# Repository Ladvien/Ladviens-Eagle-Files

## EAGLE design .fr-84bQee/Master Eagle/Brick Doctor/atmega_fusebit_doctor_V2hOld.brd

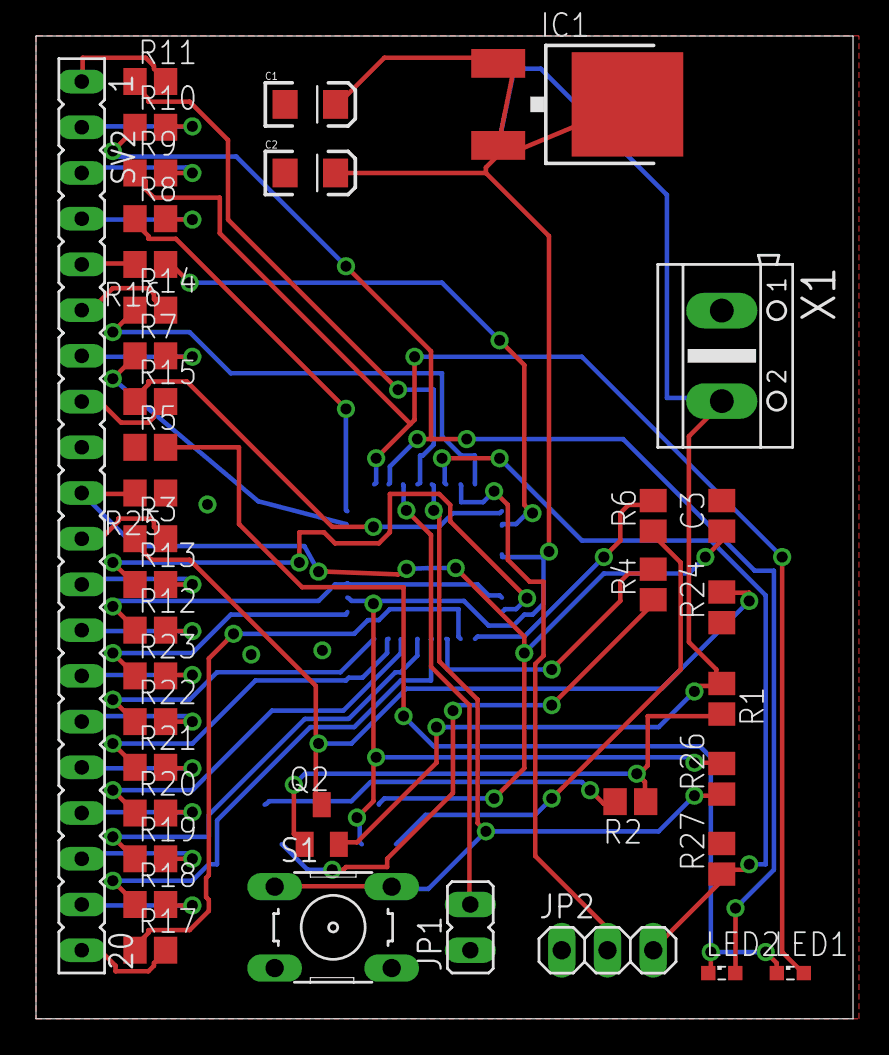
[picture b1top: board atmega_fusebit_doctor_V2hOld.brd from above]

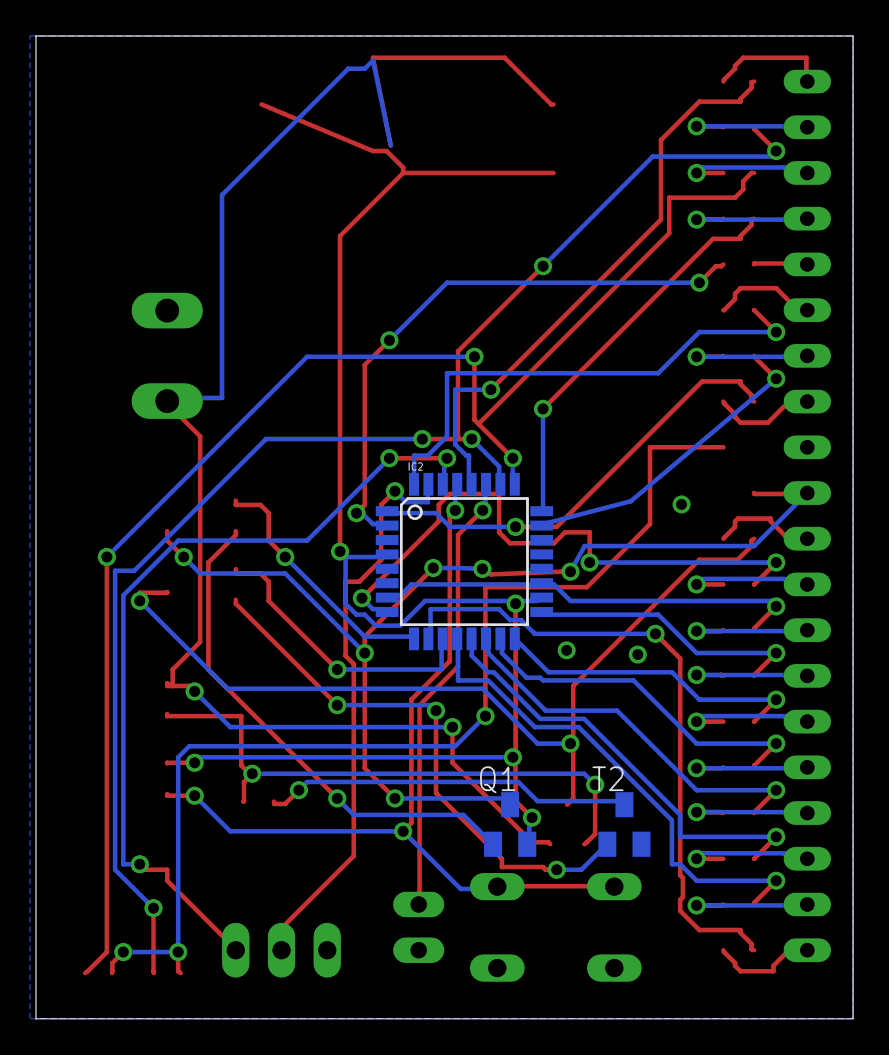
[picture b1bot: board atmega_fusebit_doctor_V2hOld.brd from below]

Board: 2 copper layers, 45.4 x 54.6 mm, 42 parts (3 on the bottom side), 51 nets.

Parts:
C1: 100uF; EIA3216
C2: 10uF; EIA3216
C3: 10nF; C0805
IC1: 7805; V-REG_DPACK
IC2: ATMEGA8-DOC; TQFP32-08
JP1: ERASE; JP1
JP2: RS232; 1X03
LED1: red; SML0603
LED2: green; SML0603
Q1, Q2: BC857ALT1SMD; SOT23-BEC
R1, R27: 10K; R0805
R2, R7, R8, R9, R10, R11, R12, R13, R14, R15, R16, R17, R18, R19, R20, R21, R22, R23, R24, R26: 1K; R0805
R3, R25: 100; R0805
R4, R6: 4K7; R0805
R5: 330; R0805
S1: START; B3F-10XX
SV2: FE20
T2: BC847; SOT23
X1: AK500/2

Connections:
+5V: C3.1, Q1.C, R25.2, SV2.10
+12V: R3.2, SV2.11
BS1: R8.2, SV2.4
BS2: R17.2, SV2.20
DATA0: R18.2, SV2.19
DATA1: R19.2, SV2.18
DATA2: R20.2, SV2.17
DATA3: R21.2, SV2.16
DATA4: R22.2, SV2.15
DATA5: R23.2, SV2.14
DATA6: R12.2, SV2.13
DATA7: R13.2, SV2.12
GND: C1.C, C2.C, C3.2, IC1.1, IC2.3, IC2.21, JP1.1, JP2.1, R5.1, R24.1, R25.1, R27.2, S1.3, S1.4, SV2.9, T2.2, X1.1
unnamed: Q1.B, R6.1
unnamed: IC2.12, R18.1
unnamed: IC2.31, JP2.2
unnamed: IC2.28, R11.1
unnamed: IC2.2, R16.1
unnamed: IC2.32, R14.1
unnamed: IC2.30, JP2.3, R27.1
unnamed: R2.2, T2.3
unnamed: IC2.7, IC2.19, R12.1
unnamed: IC2.8, R13.1
unnamed: IC2.11, R4.2
unnamed: IC2.9, R6.2
unnamed: IC2.13, R19.1
unnamed: IC2.14, R20.1
unnamed: IC2.1, R15.1
unnamed: IC2.23, R7.1
unnamed: Q2.C, R3.1, R24.2
unnamed: IC2.15, R21.1
unnamed: IC2.16, R22.1
unnamed: IC2.17, R23.1
unnamed: IC2.10, R17.1
unnamed: R4.1, T2.1
unnamed: IC2.27, JP1.2
unnamed: LED1.C, LED2.C, R5.2
unnamed: Q2.B, R1.2, R2.1
unnamed: IC2.24, R8.1
unnamed: IC2.29, R26.1, S1.1, S1.2
unnamed: IC2.26, LED2.A, R10.1
unnamed: IC2.25, LED1.A, R9.1
OE: R14.2, SV2.6
PAG: R11.2, SV2.1
RDY: R7.2, SV2.7
V+: C1.A, IC1.3, Q2.E, R1.1, X1.2
VCC: C2.A, IC1.4, IC2.4, IC2.18, Q1.E, R26.2
WR: R16.2, SV2.5
XA0: R9.2, SV2.3
XA1: R10.2, SV2.2
XTAL1: R15.2, SV2.8

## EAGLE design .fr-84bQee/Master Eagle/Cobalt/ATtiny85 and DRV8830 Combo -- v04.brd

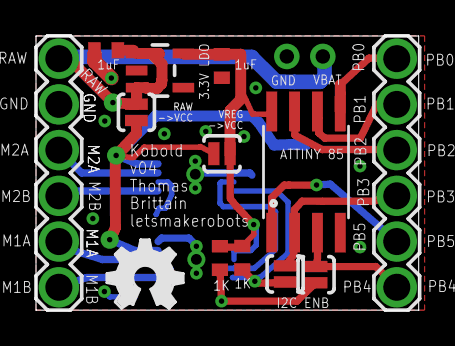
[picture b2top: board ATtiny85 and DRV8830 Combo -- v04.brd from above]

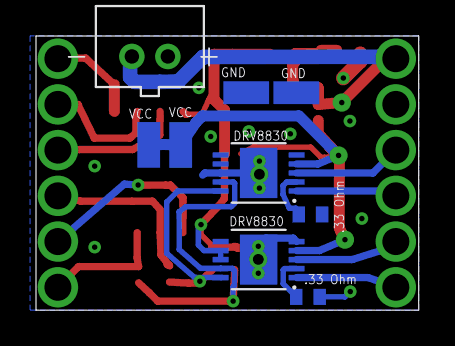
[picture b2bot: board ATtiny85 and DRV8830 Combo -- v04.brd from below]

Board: 2 copper layers, 21.3 x 15.2 mm, 22 parts (9 on the bottom side), 18 nets.

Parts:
1K: R3; R0402
C1, C2: 1uf; C0402
CN1: JST-PH-2-THM
PAD1, PAD2, PAD3, PAD4: SMD1,27-2,54
R1, R3: .33; R0402
R2: 1k; R0402
RAW: SOLDERJUMPERNO; SJ_2S-NO
SJ6, SJ7: SOLDERJUMPERNO; SJ_2S-NO
U1: V_REG_LDOSMD; SOT23-5
U2, U3: DRV8830; MSOP-10-GNDPAD
U$1, U$4: 1X6_SHORT_ROUND
U$2: ATTINY85; SO08-EIAJ
U$3: OSHW_FILLX150_NOTEXT
VREG: SOLDERJUMPERNO; SJ_2S-NO

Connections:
BAT_RAW: C1.1, CN1.2, RAW.1, U1.1, U1.3, U$4.1
GND: C1.2, C2.2, CN1.1, PAD1.1, PAD3.1, R1.1, R3.1, U1.2, U2.5, U2.GND, U3.5, U3.7, U3.8, U3.GND, U$2.4, U$4.2
M1_A: U2.3, U$4.5
M1_B: U2.1, U$4.6
M2_A: U3.3, U$4.3
M2_B: U3.1, U$4.4
unnamed: R1.2, U3.2
unnamed: R3.2, U2.2
PB0: U$1.1, U$2.5
PB1: U$1.2, U$2.6
PB2: U$1.3, U$2.7
PB3: SJ7.2, U$1.4, U$2.2
PB4: SJ6.2, U$1.6, U$2.3
PB5: U$1.5, U$2.1
SCL: R2.2, SJ7.1, U2.10, U3.10
SDA: 1K.2, SJ6.1, U2.9, U3.9
VCC: PAD2.1, PAD4.1, RAW.2, U2.4, U3.4, VREG.2
VREG: 1K.1, C2.1, R2.1, U1.5, U2.7, U2.8, U$2.8, VREG.1

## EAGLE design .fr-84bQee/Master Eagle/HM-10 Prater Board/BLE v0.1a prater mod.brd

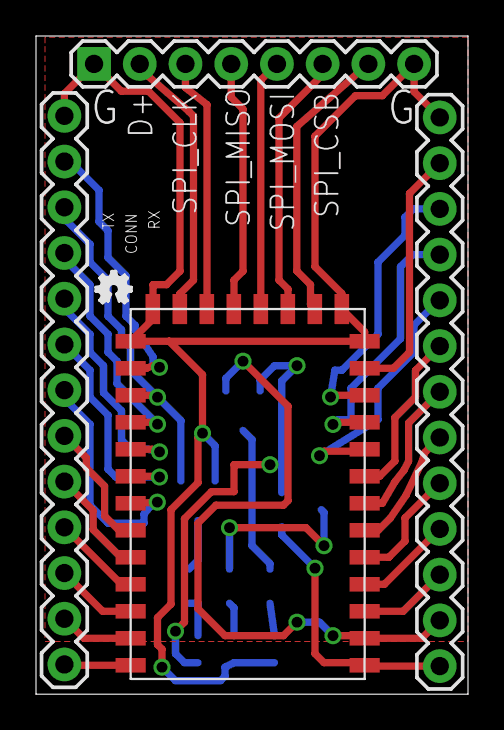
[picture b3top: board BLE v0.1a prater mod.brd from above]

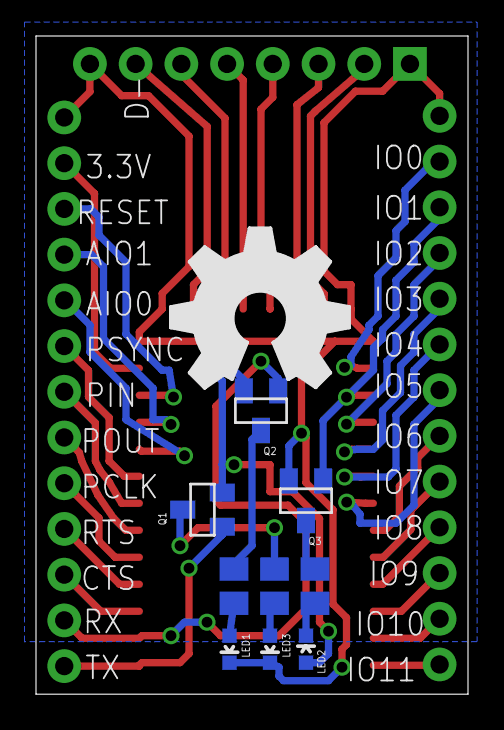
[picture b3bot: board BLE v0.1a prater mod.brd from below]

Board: 2 copper layers, 24.0 x 36.6 mm, 15 parts (10 on the bottom side), 38 nets.

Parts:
JP1, JP2: M13; 1X13
JP3: 1X08
LED1, LED2, LED3: LED-0603
Q1, Q2: MMBT3906; SOT23
Q3: MMBT2222A; SOT23
R7, R8, R9: 220; M0805
U$1: BLE-HM-10
U$2: OSHW_FILLX350_NOTEXT
U$3: OSHW_FILLX70_NOTEXT

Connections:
3.3V: LED2.A, Q1.2, Q2.2
GND: JP1.1, JP2.13, JP3.1, JP3.8, LED1.C, LED3.C, Q3.2, U$1.GND1, U$1.GND2, U$1.GND3, U$1.GND4
HVTX->LVRX: JP1.12, Q2.1, U$1.UART_RX
LVRX->HVTX: JP1.13, Q1.1, U$1.UART_TX
unnamed: Q3.3, R7.1
unnamed: JP1.3, U$1.RESET
unnamed: JP1.4, U$1.AIO1
unnamed: JP1.5, U$1.AIO0
unnamed: JP1.6, U$1.PCM_SYNC
unnamed: JP1.7, U$1.PCM_IN
unnamed: JP1.8, U$1.PCM_OUT
unnamed: JP1.9, U$1.PCM_CLK
unnamed: JP1.10, U$1.UART_RTS
unnamed: JP1.11, U$1.UART_CTS
unnamed: JP2.1, U$1.PIO11
unnamed: JP2.2, U$1.PIO10
unnamed: JP2.3, U$1.PIO9
unnamed: JP2.4, U$1.PIO8
unnamed: JP2.5, U$1.PIO7
unnamed: JP2.6, U$1.PIO6
unnamed: JP2.7, U$1.PIO5
unnamed: JP2.8, U$1.PIO4
unnamed: JP2.9, U$1.PIO3
unnamed: JP2.10, U$1.PIO2
unnamed: JP2.11, Q3.1, U$1.PIO1
unnamed: LED2.C, R7.2
unnamed: JP3.2, U$1.USB_D+
unnamed: JP3.3, U$1.SPI_CLK
unnamed: JP3.4, U$1.SPI_MISO
unnamed: JP3.5, U$1.SPI_MOSI
unnamed: JP3.6, U$1.SPI_CSB
unnamed: JP3.7, U$1.USB_D-
unnamed: Q2.3, R9.2
unnamed: LED1.A, R9.1
unnamed: LED3.A, R8.1
unnamed: Q1.3, R8.2
unnamed: JP1.2, U$1.3.3V
unnamed: JP2.12, U$1.PIO0

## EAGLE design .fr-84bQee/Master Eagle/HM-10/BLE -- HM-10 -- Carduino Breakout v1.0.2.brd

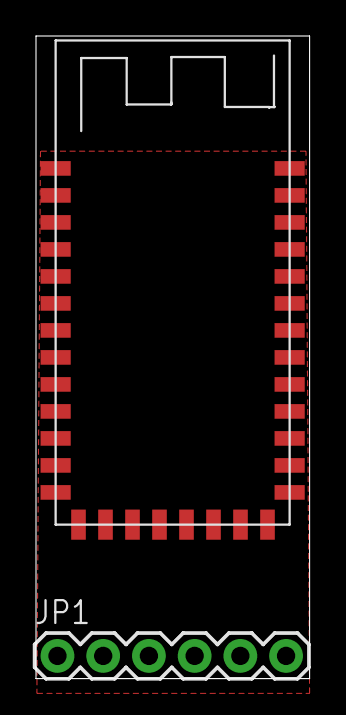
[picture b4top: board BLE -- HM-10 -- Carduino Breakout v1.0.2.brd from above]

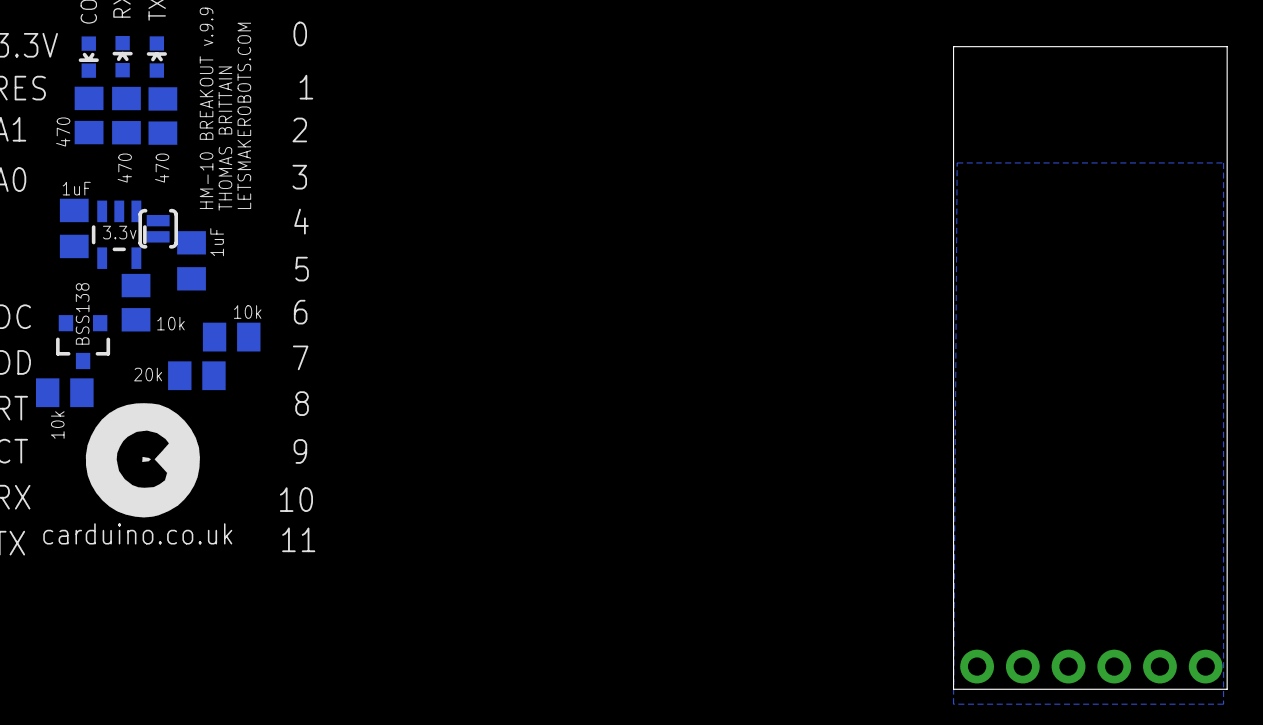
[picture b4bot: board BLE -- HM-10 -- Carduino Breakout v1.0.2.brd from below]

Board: 2 copper layers, 15.2 x 35.7 mm, 18 parts (15 on the bottom side), 11 nets, no tracks yet.

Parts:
BSS138: MOSFET-NCHANNELSMD; SOT23-3
C1, C2: 1uF; C0805K
CONN_LED: LED-0603
JP1: 1X06
R1, R2: 1k; M0805
R3, R5, R6: 10k; M0805
R4: 20k; M0805
R7: 220; M0805
RX_LED: LED-0603
SJ1: SOLDERJUMPERNO; SJ_2S-NO
TX_LED: LED-0603
U1: V_REG_LDOSMD; SOT23-5
U$1: BLE-HM-10
U$3: OSHW_FILLX70_NOTEXT

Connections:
3_3V: BSS138.1, C2.1, R1.2, R2.2, R6.2, SJ1.1, U1.5, U$1.3.3V
5V: C1.1, R5.2, SJ1.2, U1.1, U1.3
GND: C1.2, C2.2, R4.2, R7.1, U1.2, U$1.GND1, U$1.GND2, U$1.GND3, U$1.GND4
HVTX->LVRX: R3.2, R4.1, U$1.UART_RX
LVRX->HVTX: BSS138.2, R6.1, U$1.UART_TX
unnamed: CONN_LED.A, U$1.PIO1
unnamed: R1.1, TX_LED.A
unnamed: CONN_LED.C, R7.2
unnamed: R2.1, RX_LED.A
RX: R3.1, RX_LED.C
TX: BSS138.3, R5.1, TX_LED.C

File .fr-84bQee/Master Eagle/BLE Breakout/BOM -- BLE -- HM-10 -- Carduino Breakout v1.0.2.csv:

"Part";"Value";"Device";"Package";"Description";"";
"BSS138";"MOSFET-NCHANNELSMD";"MOSFET-NCHANNELSMD";"SOT23-3";"";"";
"C1";"1uF";"C-USC0805K";"C0805K";"CAPACITOR, American symbol";"";
"C2";"1uF";"C-USC0805K";"C0805K";"CAPACITOR, American symbol";"";
"CONN_LED";"";"LED0603";"LED-0603";"LEDs";"";
"JP1";"M13";"M13";"1X13";"";"";
"JP2";"M13";"M13";"1X13";"";"";
"JP3";"";"M081X08";"1X08";"Header 8";"";
"R1";"470";"R-US_M0805";"M0805";"RESISTOR, American symbol";"";
"R2";"470";"R-US_M0805";"M0805";"RESISTOR, American symbol";"";
"R3";"10k";"R-US_M0805";"M0805";"RESISTOR, American symbol";"";
"R4";"20k";"R-US_M0805";"M0805";"RESISTOR, American symbol";"";
"R5";"10k";"R-US_M0805";"M0805";"RESISTOR, American symbol";"";
"R6";"10k";"R-US_M0805";"M0805";"RESISTOR, American symbol";"";
"R7";"470";"R-US_M0805";"M0805";"RESISTOR, American symbol";"";
"RX_LED";"";"LED0603";"LED-0603";"LEDs";"";
"SJ1";"SOLDERJUMPERNO";"SOLDERJUMPERNO";"SJ_2S-NO";"Solder Jumper";"";
"TX_LED";"";"LED0603";"LED-0603";"LEDs";"";
"U$1";"BLE-HM-10";"BLE-HM-10";"BLE-HM-10";"";"";
"U1";"V_REG_LDOSMD";"V_REG_LDOSMD";"SOT23-5";"Voltage Regulator LDO";"";

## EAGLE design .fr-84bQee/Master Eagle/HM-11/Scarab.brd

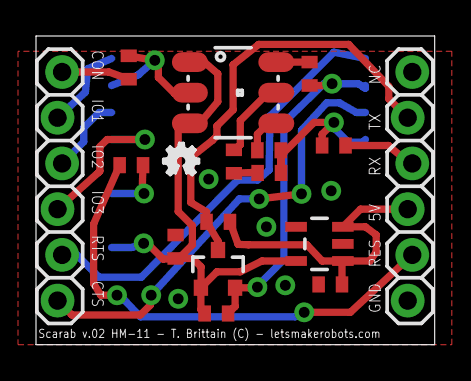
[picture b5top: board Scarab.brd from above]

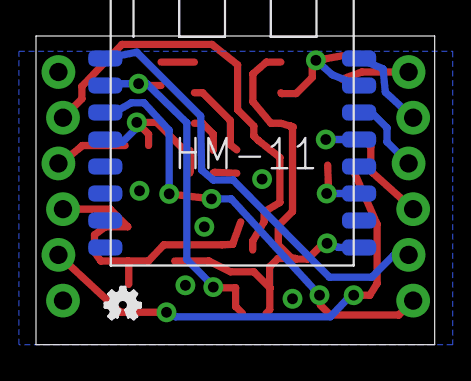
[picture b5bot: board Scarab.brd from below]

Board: 2 copper layers, 22.1 x 17.1 mm, 19 parts (2 on the bottom side), 19 nets.

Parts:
BSS138: MOSFET-NCHANNELSMD; SOT23-3
C1, C2: 1uF; C0402
JP1, JP2: 1X06_LOCK
LED1: LED-TRICOLOR-5050NO_IC; LED-TRICOLOR-5050
R1, R2, R7: 470; R0402
R3, R5, R6: 10k; R0402
R4: 20k; R0402
R8, R9: 10K; R0402
U1: V_REG_LDOSMD; SOT23-5
U$1: HM-11
U$3, U$4: OSHW_FILLX70_NOTEXT

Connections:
3_3V: BSS138.1, C2.1, LED1.1, LED1.3, R6.2, U1.5, U$1.9
5V: C1.1, JP1.3, R5.2, U1.1, U1.3
CONN_PIN: LED1.2, R8.2, U$1.15
CONN_STAT: JP2.1, R8.1
CTS: JP2.6, U$1.3
GND: C1.2, C2.2, JP1.1, R4.2, R7.1, U1.2, U$1.12
IO0: JP2.2, U$1.16
IO2: JP2.3, U$1.14
IO3: JP2.4, U$1.13
unnamed: LED1.6, R1.2
unnamed: LED1.4, R2.2
unnamed: LED1.5, R7.2
RES: R9.1, U$1.11
RES_C: JP1.2, R9.2
RTS: JP2.5, U$1.1
RX: JP1.4, R3.1
RX-3.3V: R2.1, R3.2, R4.1, U$1.4
TX: BSS138.3, JP1.5, R5.1
TX-3.3V: BSS138.2, R1.1, R6.1, U$1.2

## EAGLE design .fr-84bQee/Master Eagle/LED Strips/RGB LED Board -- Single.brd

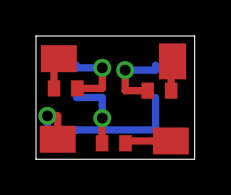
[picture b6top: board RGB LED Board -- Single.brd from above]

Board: 2 copper layers, 8.8 x 6.8 mm, 8 parts (1 on the bottom side), 7 nets.

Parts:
JP1, JP2, JP3, JP4: M01SMD-4.5X1.5; PAD-1.5X4.5
LED2: LED-TRICOLOR-5050
R2, R3, R4: R0402

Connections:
unnamed: LED2.2, R2.2
unnamed: LED2.1, R3.2
unnamed: LED2.3, R4.2
unnamed: JP2.P$1, LED2.4, LED2.5, LED2.6
unnamed: JP1.P$1, R2.1
unnamed: JP3.P$1, R3.1
unnamed: JP4.P$1, R4.1

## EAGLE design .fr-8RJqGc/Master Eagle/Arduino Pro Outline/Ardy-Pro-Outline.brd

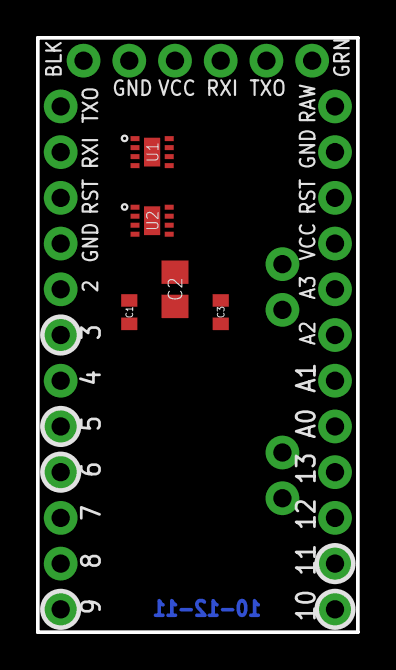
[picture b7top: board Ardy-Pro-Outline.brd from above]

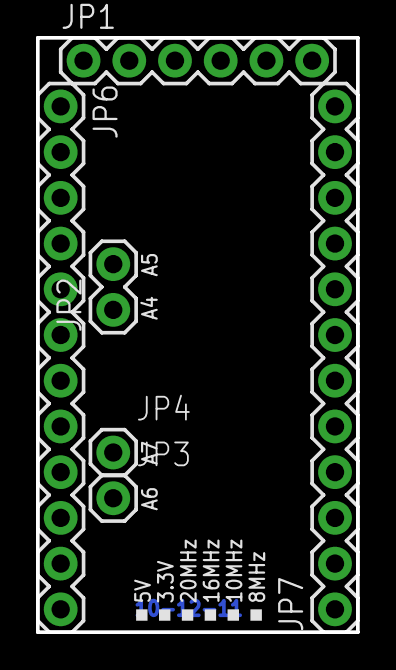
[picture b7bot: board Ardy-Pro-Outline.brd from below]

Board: 2 copper layers, 17.8 x 33.0 mm, 11 parts (6 on the bottom side), 6 nets, no tracks yet.

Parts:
C1, C3: 0.1uF; C0402
C2: 10uF; C0805
JP1: FTDI Basic; 1X06
JP2: 1X02
JP3, JP4: 1X01
JP6, JP7: 1X12
U1, U2: DRV8837; WSON-8

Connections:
GND: C1.2, JP1.5, JP1.6, JP6.2, JP7.9, U1.4, U1.9, U2.4
RESET: JP6.3, JP7.10
RXI: JP1.3, JP7.11
TXO: JP1.2, JP7.12
VCC: C1.1, C3.1, JP1.4, JP6.4, U1.8, U2.8
VM: U1.1, U2.1

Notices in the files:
parts and their libraries:
SparkFun: Licensing: CC v3.0 Share-Alike You are welcome to use this library for commercial purposes.
SparkFun-Connectors: Licensing: Creative Commons ShareAlike 4.0 International - https://creativecommons.org/licenses/by-sa/4.0
